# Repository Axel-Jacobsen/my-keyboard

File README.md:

# Plan

split keyboard, fun to make and fun to have

TODOs
=====
[ ] swap to low profile keys
[ ] expose scl, sda
[ ] tighten up PCB

microcontroller
===============
- connection type
  - wired
    - pros: no battery, simpler, would be fun to program bluetooth controller
    - cons: annoying while using
  - bluetooth:
    - pros: clean to use
    - cons: battery is annoying
  - *decision*
    - wired to start[0] - bluetooth will make the project more complicated than necessary
- possible options
  - ATmega32U4 (widely used, looks small)
    - as raw IC mounted on the PCB (more complicated, so don't do) or as a "hat" on a breakout board
      - https://www.microchip.com/en-us/product/atmega32u4
      - https://learn.sparkfun.com/tutorials/pro-micro--fio-v3-hookup-guide/hardware-overview-pro-micro
  - STM32F103 (powerful, bigger)
- microcontroller -> pcb - how to connect?
  - solder directly to pcb
    - pros: fuckin sick, may be cheaper? maybe not
    - cons: much more difficult to manufacture
  - get breakout and solder the pins
    - pros: much easier to deal with
    - cons: less fkn tight
  - *decision*
    - do breakout for v1
- *variables to minimize*
  - size
  - power consumption
  - key-press latency

eece / computer
===============
- need to be able to detect any combination of keys together simultaneously
- sw
  - rust ;)
    - avr rust book: https://book.avr-rust.org/
    - https://docs.rs/avrd/latest/avrd/atmega16u4/index.html
  - implements USB HID 1.11 + reading gpio inputs
- elec
  - nice looking pcb
  - reading keys
    - keyboard matrix
      - pros: simple
    - shift registers (74HC165) to multiplex data in
      - pros: sort of more interesting
    - *decision*
      - keyboard matrix. simpler is better.
  - is there a little led grid that I could have sitting somewhere flashing when keys are pressed?

keys + key caps
===============

- A 61 key keyboard is common - a "60%" - but what do I need?
  - want 60 keys minimum
    - 26 for the letters of the alphabet
    - 10 for decimal digits
    - 1 for +
    - 1 for -
    - 1 for spacebar
    - 3 for control, option, command
    - 1 for escape (in caps lock position)
    - 1 for tilde
    - 1 for tab
    - 1 for shift
    - 1 for ;
    - 1 for '
    - 1 for delete
    - 2 for <>
    - 2 for []
    - 1 for ?
    - 1 for \
    - 4 for arrow keys
    - 1 for special key 1
  - with another 5,
    - 1 for split spacebar
    - 1 for another special key
    - ??? three fun extra keys
- key type
  - mechanical keys
    - pros: maybe sounds good
    - cons: misclick frequently, more tiring to type, slow
  - flat keys
    - pros: easier to press, faster to type
    - cons: less cool?
  - *decision*
    - search for flat keys and mechanical keys, should be able to make keybaords with either in the same way

[1]: https://www.digikey.com/en/products/detail/gct/USB4085-GF-A/9859662

[0]: [usb c breakout](https://tinyurl.com/269dkzz5) or [this full breakout](https://www.adafruit.com/product/4396#description)

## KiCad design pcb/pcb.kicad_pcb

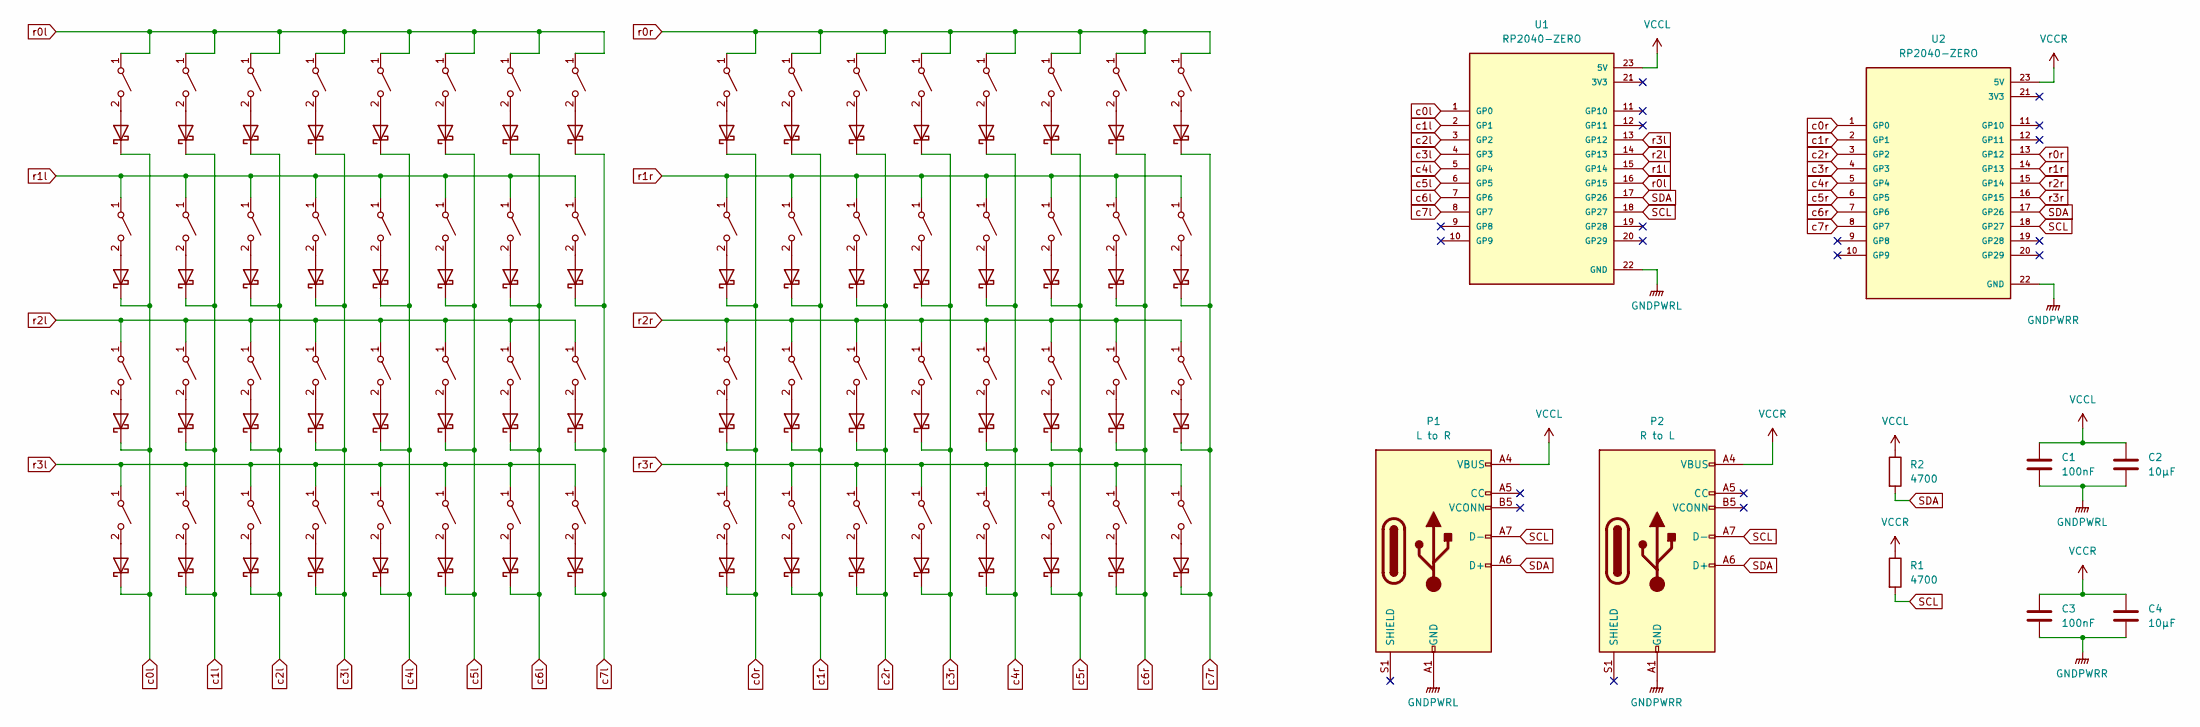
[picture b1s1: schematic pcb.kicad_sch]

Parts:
C1, C3: 100nF; C_1206_3216Metric_Pad1.33x1.80mm_HandSolder
C2, C4: 10µF; C_1206_3216Metric_Pad1.33x1.80mm_HandSolder
D1, D2, D3, D4, D5, D6, D7, D8, D9, D10, D11, D12, D13, D14, D15, D16, D17, D18, D19, D20, D21, D22, D23, D24, D25, D26, D27, D28, D29, D30, D31, D32, D33, D34, D35, D36, D37, D38, D39, D40, D41, D42, D43, D44, D45, D46, D47, D48, D49, D50, D51, D52, D53, D54, D55, D56, D57, D58, D59, D60, D61, D62, D63, D64: 1N5817; D_DO-41_SOD81_P10.16mm_Horizontal
P1: L to R; USB_C_Receptacle_GCT_USB4085
P2: R to L; USB_C_Receptacle_GCT_USB4085
R1, R2: 4700; R_1206_3216Metric_Pad1.30x1.75mm_HandSolder
SW1, SW2, SW3, SW4, SW5, SW6, SW7, SW8, SW9, SW10, SW11, SW12, SW13, SW14, SW15, SW16, SW17, SW18, SW19, SW20, SW21, SW22, SW23, SW24, SW25, SW26, SW27, SW28, SW29, SW30, SW31, SW32, SW33, SW34, SW35, SW36, SW37, SW38, SW39, SW40, SW41, SW42, SW43, SW44, SW45, SW46, SW47, SW48, SW49, SW50, SW51, SW52, SW53, SW54, SW55, SW56, SW57, SW58, SW59, SW60, SW61, SW62, SW63, SW64: SW_SPST; SW_Kailh_Choc_V2_THT
U1, U2: RP2040-ZERO; MODULE_RP2040-ZERO; PARTREV NA

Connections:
GNDPWRL: C1.2, C2.2, P1.A1 (GND), P1.A12 (GND), P1.B1 (GND), P1.B12 (GND), U1.22 (GND)
GNDPWRR: C3.2, C4.2, P2.A1 (GND), P2.A12 (GND), P2.B1 (GND), P2.B12 (GND), U2.22 (GND)
unnamed: D1.2 (A), SW1.2 (B)
unnamed: D2.2 (A), SW2.2 (B)
unnamed: D3.2 (A), SW3.2 (B)
unnamed: D4.2 (A), SW4.2 (B)
unnamed: D5.2 (A), SW5.2 (B)
unnamed: D6.2 (A), SW6.2 (B)
unnamed: D7.2 (A), SW7.2 (B)
unnamed: D8.2 (A), SW8.2 (B)
unnamed: D9.2 (A), SW9.2 (B)
unnamed: D10.2 (A), SW10.2 (B)
unnamed: D11.2 (A), SW11.2 (B)
unnamed: D12.2 (A), SW12.2 (B)
unnamed: D13.2 (A), SW13.2 (B)
unnamed: D14.2 (A), SW14.2 (B)
unnamed: D15.2 (A), SW15.2 (B)
unnamed: D16.2 (A), SW16.2 (B)
unnamed: D17.2 (A), SW17.2 (B)
unnamed: D18.2 (A), SW18.2 (B)
unnamed: D19.2 (A), SW19.2 (B)
unnamed: D20.2 (A), SW20.2 (B)
unnamed: D21.2 (A), SW21.2 (B)
unnamed: D22.2 (A), SW22.2 (B)
unnamed: D23.2 (A), SW23.2 (B)
unnamed: D24.2 (A), SW24.2 (B)
unnamed: D25.2 (A), SW25.2 (B)
unnamed: D26.2 (A), SW26.2 (B)
unnamed: D27.2 (A), SW27.2 (B)
unnamed: D28.2 (A), SW28.2 (B)
unnamed: D29.2 (A), SW29.2 (B)
unnamed: D30.2 (A), SW30.2 (B)
unnamed: D31.2 (A), SW31.2 (B)
unnamed: D32.2 (A), SW32.2 (B)
unnamed: D33.2 (A), SW33.2 (B)
unnamed: D34.2 (A), SW34.2 (B)
unnamed: D35.2 (A), SW35.2 (B)
unnamed: D36.2 (A), SW36.2 (B)
unnamed: D37.2 (A), SW37.2 (B)
unnamed: D38.2 (A), SW38.2 (B)
unnamed: D39.2 (A), SW39.2 (B)
unnamed: D40.2 (A), SW40.2 (B)
unnamed: D41.2 (A), SW41.2 (B)
unnamed: D42.2 (A), SW42.2 (B)
unnamed: D43.2 (A), SW43.2 (B)
unnamed: D44.2 (A), SW44.2 (B)
unnamed: D45.2 (A), SW45.2 (B)
unnamed: D46.2 (A), SW46.2 (B)
unnamed: D47.2 (A), SW47.2 (B)
unnamed: D48.2 (A), SW48.2 (B)
unnamed: D49.2 (A), SW49.2 (B)
unnamed: D50.2 (A), SW50.2 (B)
unnamed: D51.2 (A), SW51.2 (B)
unnamed: D52.2 (A), SW52.2 (B)
unnamed: D53.2 (A), SW53.2 (B)
unnamed: D54.2 (A), SW54.2 (B)
unnamed: D55.2 (A), SW55.2 (B)
unnamed: D56.2 (A), SW56.2 (B)
unnamed: D57.2 (A), SW57.2 (B)
unnamed: D58.2 (A), SW58.2 (B)
unnamed: D59.2 (A), SW59.2 (B)
unnamed: D60.2 (A), SW60.2 (B)
unnamed: D61.2 (A), SW61.2 (B)
unnamed: D62.2 (A), SW62.2 (B)
unnamed: D63.2 (A), SW63.2 (B)
unnamed: D64.2 (A), SW64.2 (B)
SCL: P1.A7 (D-), P2.A7 (D-), R1.2, U1.18 (GP27), U2.18 (GP27)
SDA: P1.A6 (D+), P2.A6 (D+), R2.2, U1.17 (GP26), U2.17 (GP26)
VCCL: C1.1, C2.1, P1.A4 (VBUS), P1.A9 (VBUS), P1.B4 (VBUS), P1.B9 (VBUS), R2.1, U1.23 (5V)
VCCR: C3.1, C4.1, P2.A4 (VBUS), P2.A9 (VBUS), P2.B4 (VBUS), P2.B9 (VBUS), R1.1, U2.23 (5V)
c0l: D1.1 (K), D2.1 (K), D3.1 (K), D4.1 (K), U1.1 (GP0)
c0r: D6.1 (K), D12.1 (K), D18.1 (K), D24.1 (K), U2.1 (GP0)
c1l: D7.1 (K), D8.1 (K), D9.1 (K), D10.1 (K), U1.2 (GP1)
c1r: D30.1 (K), D36.1 (K), D37.1 (K), D38.1 (K), U2.2 (GP1)
c2l: D13.1 (K), D14.1 (K), D15.1 (K), D16.1 (K), U1.3 (GP2)
c2r: D39.1 (K), D40.1 (K), D41.1 (K), D42.1 (K), U2.3 (GP2)
c3l: D19.1 (K), D20.1 (K), D21.1 (K), D22.1 (K), U1.4 (GP3)
c3r: D43.1 (K), D44.1 (K), D45.1 (K), D46.1 (K), U2.4 (GP3)
c4l: D25.1 (K), D26.1 (K), D27.1 (K), D28.1 (K), U1.5 (GP4)
c4r: D47.1 (K), D48.1 (K), D49.1 (K), D50.1 (K), U2.5 (GP4)
c5l: D31.1 (K), D32.1 (K), D33.1 (K), D34.1 (K), U1.6 (GP5)
c5r: D51.1 (K), D52.1 (K), D53.1 (K), D54.1 (K), U2.6 (GP5)
c6l: D5.1 (K), D11.1 (K), D17.1 (K), D23.1 (K), U1.7 (GP6)
c6r: D55.1 (K), D56.1 (K), D57.1 (K), D58.1 (K), U2.7 (GP6)
c7l: D29.1 (K), D35.1 (K), D61.1 (K), D62.1 (K), U1.8 (GP7)
c7r: D59.1 (K), D60.1 (K), D63.1 (K), D64.1 (K), U2.8 (GP7)
r0l: SW1.1 (A), SW5.1 (A), SW7.1 (A), SW13.1 (A), SW19.1 (A), SW25.1 (A), SW29.1 (A), SW31.1 (A), U1.16 (GP15)
r0r: SW6.1 (A), SW30.1 (A), SW39.1 (A), SW43.1 (A), SW47.1 (A), SW51.1 (A), SW55.1 (A), SW59.1 (A), U2.13 (GP12)
r1l: SW2.1 (A), SW8.1 (A), SW11.1 (A), SW14.1 (A), SW20.1 (A), SW26.1 (A), SW32.1 (A), SW35.1 (A), U1.15 (GP14)
r1r: SW12.1 (A), SW36.1 (A), SW40.1 (A), SW44.1 (A), SW48.1 (A), SW52.1 (A), SW56.1 (A), SW60.1 (A), U2.14 (GP13)
r2l: SW3.1 (A), SW9.1 (A), SW15.1 (A), SW17.1 (A), SW21.1 (A), SW27.1 (A), SW33.1 (A), SW61.1 (A), U1.14 (GP13)
r2r: SW18.1 (A), SW37.1 (A), SW41.1 (A), SW45.1 (A), SW49.1 (A), SW53.1 (A), SW57.1 (A), SW63.1 (A), U2.15 (GP14)
r3l: SW4.1 (A), SW10.1 (A), SW16.1 (A), SW22.1 (A), SW23.1 (A), SW28.1 (A), SW34.1 (A), SW62.1 (A), U1.13 (GP12)
r3r: SW24.1 (A), SW38.1 (A), SW42.1 (A), SW46.1 (A), SW50.1 (A), SW54.1 (A), SW58.1 (A), SW64.1 (A), U2.16 (GP15)

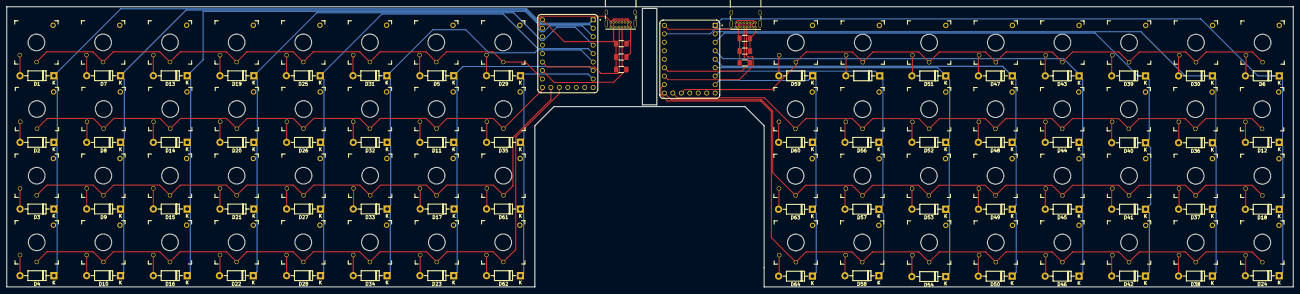
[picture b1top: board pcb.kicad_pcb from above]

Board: 2 copper layers, 386.1 x 84.1 mm, 138 parts (0 on the bottom side), 94 nets.

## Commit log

2024-10-01 layout
2024-10-01 add doc
2024-10-02 save pcb
2025-03-10 sanity save
2025-03-10 updad
2025-03-17 upd and add switches submodule
2025-03-18 cleans
2025-05-10 a lot of updates
2025-05-10 yooooo thankn you gpt
2025-05-11 lfgooooo
2025-05-11 think it si there
2025-05-18 about tod o smth dumb
2025-05-18 to low prof
2025-05-18 agh need to retrace some stuff will do tmmr
2025-05-19 fxes
2025-05-24 iguess
2025-06-23 init
2025-06-28 need these
2025-07-29 wahoo
2025-07-29 uhidk
2025-07-29 letsgooo
2025-07-30 ahhh you must release it! release!
2025-07-30 progress
2025-07-30 hmmm
2025-07-30 nothing yet...
2025-07-30 it is working just gotta send actual key reports
    todos:
    - map Key to actual keys
    - factor the code to make it pretty
    - figure out debouncing, etc
2025-07-31 1khz
2025-07-31 derives
